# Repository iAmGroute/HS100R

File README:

# HS100R

A custom pcb for the TP-Link HS100 and HS110 smart plugs.

### Features:

  - Uses the low power nRF51 SoC (+4dBm 2.4GHz) instead of a WiFi module.
    Compatible with the popular nRF24 series modules.

  - Maintains the features of the original HS100.

  - Added sensors:

Sensor      | MPN
------------|-----
Light       | LTR-30XALS
Pressure    | DPS310
Humidity    | SI7006-A20
Temperature | SI7006-A20

  - Adds low frequency front end for mains Voltage and Current sensing, wired to the ADC of the nRF51:
    The idea is to function as a very basic oscilloscope.
    Full bandwidth: 10 KHz
      A gpio is wired to a capacitor at the input of the ADC, so that the bandwidth can be limited to around 1 KHz on demand.
    Sampling frequency: around 40 KSps (at 8 bits, around half at 10 bits)
    For the current sensing side, a current shunt resistor is required at the relay's board
    (already installed on the HS110 - 1 mOhm, will require cutting the board on the HS100 - 4 mOhm recommended)
    Two low noise PGAs (MAX9939) are added in series to give a high dynamic range.
    Max gain limitted by the front PGA's noise at around 3000x (measures a few tens of mA with 4 mOhm shunt)

  - The above can also be used to do Point-on-Wave switching:
    Turn the relay on when the instantaneous voltage is near zero
    and turn it off when the instantaneous current is near zero.
    This is done to prevend arcing on the contacts of the relay and greately improve its life span
    especially when switching heavy loads.

### Prototype pictures and screenshots:

Comming soon !

### Note about revisions:

Revisions that begin with 0 (e.g. Rev0B) are prototypes and only for reference and development.
No fully working design is available yet.

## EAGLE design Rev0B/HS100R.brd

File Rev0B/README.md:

# HS100R Rev0B  
  
Status: Unfinished  
  
TODO:  
  
  - Remove SD card slot, or reposition it.  
  
  - Fix the area of the DPS310. (maybe switch to a different IC ?)  
  
  - Reevaluate the ground layer around the DPS310.

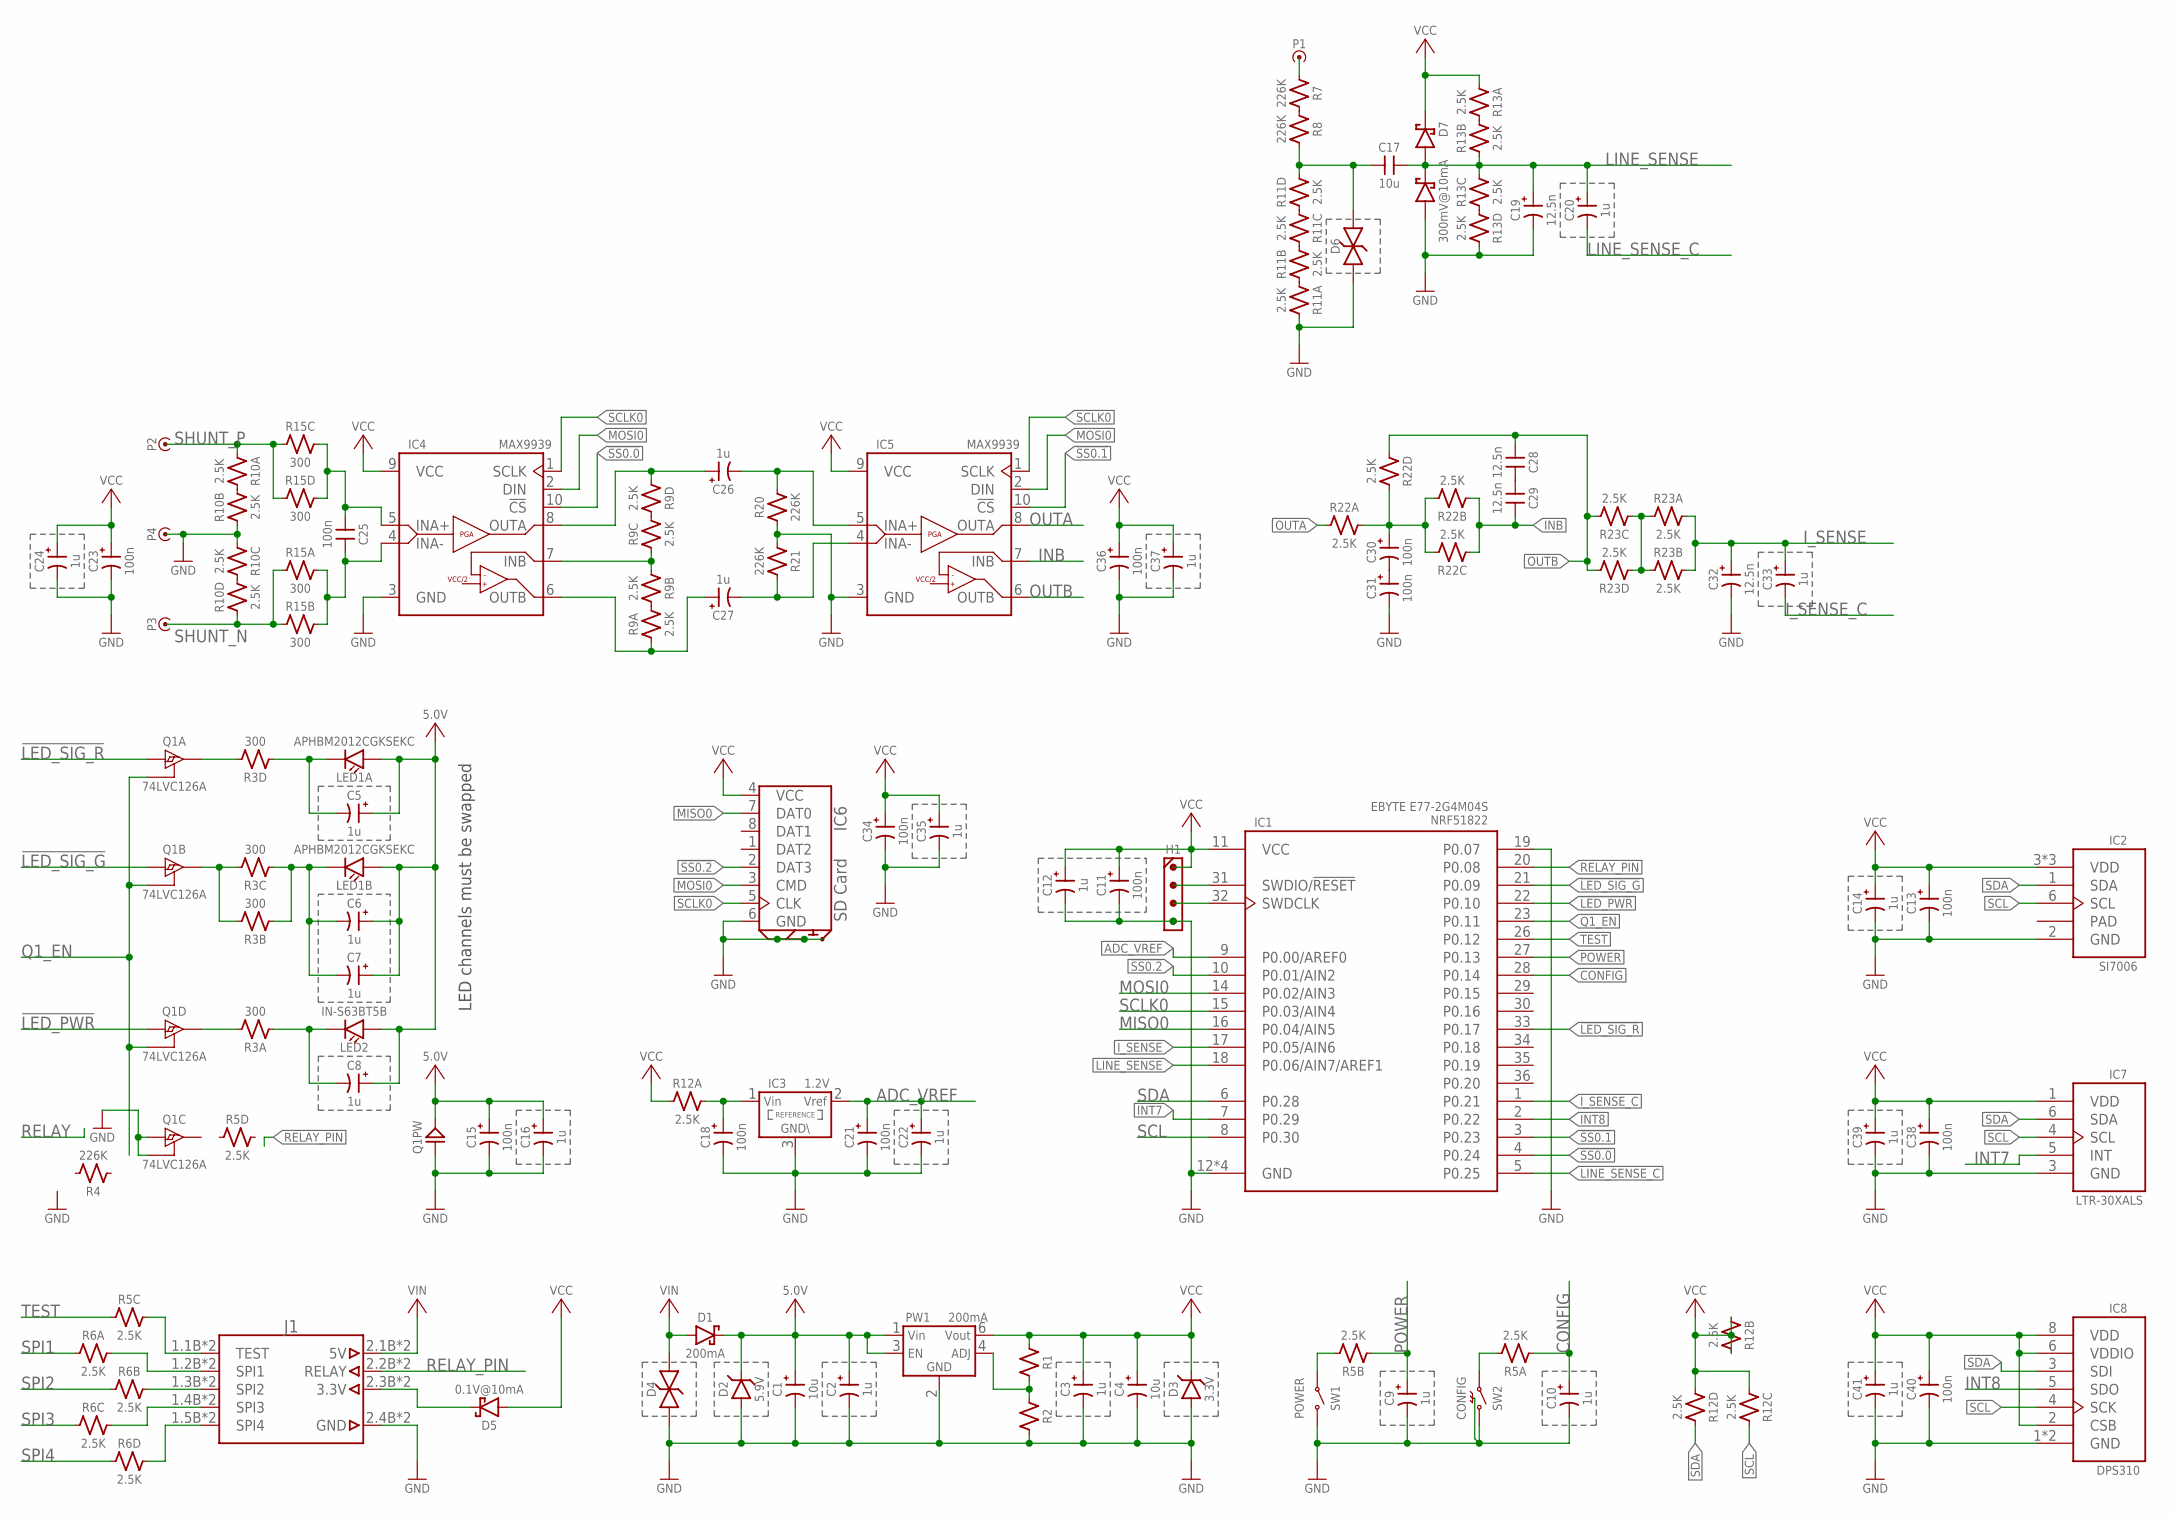
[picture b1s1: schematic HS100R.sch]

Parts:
C1, C4, C17: 10u; 1206
C2, C3, C5, C6, C7, C8, C9, C10, C12, C14, C16, C20, C22, C24, C26, C27, C33, C35, C37, C39, C41: 1u; 0805
C11, C13, C15, C18, C21, C23, C25, C30, C31, C34, C36, C38, C40: 100n; 0603
C19, C28, C29, C32: 12.5n; 0603
D1: 200mA; SOD-323F
D2: 5.9V; SOD-323F
D3: 3.3V; SOD-323F
D4, D6: DIODE_TVS_SOD-323F; SOD-323F
D5: 0.1V@10mA; SOD-323F
D7: 300mV@10mA; SOT-23
H1: HEADER_4X1-4X1; PIN_1_4X1
IC1: EBYTE_E77-2G4M04S
IC2: SI7006-A20; DFN-6_3.0_PAD
IC3: 1.2V; SOT-23
IC4, IC5: MAX9939_UMAX-10; UMAX-10
IC6: SD-CARD-MICRO-B; SD-MICRO-SPRINGED-B
IC7: LTR-30XALS
IC8: DPS310; LGA-8_2.0X2.5_0.65
J1: PCB_CONNECTOR
LED1: APHBM2012CGKSEKC; LED_DUAL-2.00X1.25
LED2: IN-S63BT5B; 0603
P1, P2, P3, P4: PIN-PIN_R_0.6; PIN_R_0.6_1X1
PW1: 200mA; SOT-23-5
Q1: 74LVC126A; SSOP-14_4.4
R1, R2: RESISTOR-0603; 0603
R3, R15: 300; 1206-QUAD
R4, R7, R8, R20, R21: 226K; 1206
R5, R6, R9, R10, R11, R12, R13, R22, R23: 2.5K; 1206-QUAD
SW1: POWER; GULLWING-4_4.2X3.2
SW2: CONFIG; SWITCH-RA_4.5X4.5

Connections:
5.0V: C1.C, C2.C, C5.C, C6.C, C7.C, C8.C, C15.C, C16.C, D1.C, D2.C, LED1.A1 (ANODE), LED1.A2 (ANODE), LED2.A (ANODE), PW1.1 (VIN), PW1.3 (EN), Q1.14 (VCC)
!LED_PWR: IC1.22 (P0.10), Q1.12 (IN)
!LED_SIG_G: IC1.21 (P0.09), Q1.5 (IN)
!LED_SIG_R: IC1.33 (P0.17), Q1.2 (IN)
!SS0.0: IC1.4 (P0.24), IC4.10 (!CS)
!SS0.1: IC1.3 (P0.23), IC5.10 (!CS)
!SS0.2: IC1.10 (P0.01/AIN2), IC6.2 (DAT3)
ADC_VREF: C21.C, C22.C, IC1.9 (P0.00/AREF0), IC3.2 (VOUT)
CONFIG: C10.C, IC1.28 (P0.14), R5.1
GND: C1.A (N), C2.A (N), C3.A (N), C4.A (N), C9.A (N), C10.A (N), C11.A (N), C12.A (N), C13.A (N), C14.A (N), C15.A (N), C16.A (N), C18.A (N), C19.A (N), C21.A (N), C22.A (N), C23.A (N), C24.A (N), C31.A (N), C32.A (N), C34.A (N), C35.A (N), C36.A (N), C37.A (N), C38.A (N), C39.A (N), C40.A (N), C41.A (N), D2.A, D3.A, D4.A (1), D6.A (1), D7.1 (A), H1.1.4, IC1.12 (GND), IC1.13 (GND), IC1.19 (P0.07), IC1.24 (GND), IC1.25 (GND), IC2.2 (GND), IC3.3 (GND), IC4.3 (GND), IC5.3 (GND), IC6.6 (GND), IC6.DETECT (DETECT1), IC6.SHIELD1 (SHIELD), IC6.SHIELD2 (SHIELD), IC6.SHIELD3 (SHIELD), IC6.SHIELD4 (DETECT2), IC7.3 (GND), IC8.1 (GND), IC8.7 (GND), J1.2.4B (GND), J1.2.4T (GND), P4.1.1, PW1.2 (GND), Q1.7 (GND), Q1.9 (IN), Q1.10 (OE), R2.C (2), R10.2 (1), R10.3 (1), R11.8 (2), R13.5 (2), R20.A (1), R21.A (1), SW1.3 (2), SW1.4 (2), SW2.2, SW2.SHIELD
INB: C29.C (2), IC5.7 (INB), R22.2 (1), R22.3 (1)
INT7: IC1.7 (P0.29), IC7.5 (INT)
INT8: IC1.2 (P0.22), IC8.5 (SDO)
I_SENSE: C32.C, C33.C, IC1.17 (P0.05/AIN6), R23.7 (2), R23.8 (2)
I_SENSE_C: C33.A (N), IC1.1 (P0.21)
LINE_SENSE: C17.C (2), C19.C, C20.C, D7.3 (COMMON), IC1.18 (P0.06/AIN7/AREF1), R13.2 (1), R13.6 (2)
LINE_SENSE_C: C20.A (N), IC1.5 (P0.25)
MISO0: IC1.16 (P0.04/AIN5), IC6.7 (DAT0)
MOSI0: IC1.14 (P0.02/AIN3), IC4.2 (DIN), IC5.2 (DIN), IC6.3 (CMD)
unnamed: D5.C, J1.2.3B (3.3V), J1.2.3T (3.3V)
unnamed: Q1.3 (OUT), R3.5 (2)
unnamed: PW1.4 (ADJ), R1.C (2), R2.A (1)
unnamed: C5.A (N), LED1.K1 (CATHODE), R3.4 (1)
unnamed: Q1.11 (OUT), R3.8 (2)
unnamed: Q1.6 (OUT), R3.6 (2), R3.7 (2)
unnamed: C8.A (N), LED2.C (CATHODE), R3.1
unnamed: J1.1.2B (SPI1), J1.1.2T (SPI1), R6.8 (2)
unnamed: C6.A (N), C7.A (N), LED1.K2 (CATHODE), R3.2 (1), R3.3 (1)
unnamed: R5.7 (2), SW1.1, SW1.2 (1)
unnamed: R11.3 (1), R11.4 (1)
unnamed: R5.8 (2), SW2.1
unnamed: J1.1.1B (TEST), J1.1.1T (TEST), R5.6 (2)
unnamed: J1.1.3B (SPI2), J1.1.3T (SPI2), R6.7 (2)
unnamed: J1.1.4B (SPI3), J1.1.4T (SPI3), R6.6 (2)
unnamed: J1.1.5B (SPI4), J1.1.5T (SPI4), R6.5 (2)
unnamed: P1.1.1, R7.A (1)
unnamed: R7.C (2), R8.A (1)
unnamed: H1.1.3, IC1.32 (SWDCLK)
unnamed: H1.1.2, IC1.31 (SWDIO/!RESET)
unnamed: C17.A (1), D6.C (2), R8.C (2), R11.5 (2)
unnamed: C18.C, IC3.1 (VIN), R12.8 (2)
unnamed: R13.7 (2), R13.8 (2)
unnamed: R13.3 (1), R13.4 (1)
unnamed: C25.A (1), IC4.5 (INA+), R15.5 (2), R15.6 (2)
unnamed: C25.C (2), IC4.4 (INA-), R15.7 (2), R15.8 (2)
unnamed: IC4.7 (INB), R9.2 (1), R9.3 (1)
unnamed: C28.C (2), C29.A (1)
unnamed: R11.6 (2), R11.7 (2)
unnamed: C30.C, R22.5 (2), R22.6 (2), R22.7 (2), R22.8 (2)
unnamed: C26.A (N), IC5.5 (INA+), R20.C (2)
unnamed: R23.1, R23.2 (1), R23.3 (1), R23.4 (1)
unnamed: C27.A (N), IC5.4 (INA-), R21.C (2)
unnamed: C26.C, IC4.8 (OUTA), R9.4 (1)
unnamed: R9.5 (2), R9.6 (2)
unnamed: C30.A (N), C31.C
unnamed: R9.7 (2), R9.8 (2)
unnamed: C27.C, IC4.6 (OUTB), R9.1
unnamed: R10.5 (2), R10.6 (2)
unnamed: R10.7 (2), R10.8 (2)
unnamed: R11.1, R11.2 (1)
OUTA: IC5.8 (OUTA), R22.1
OUTB: C28.A (1), IC5.6 (OUTB), R22.4 (1), R23.5 (2), R23.6 (2)
POWER: C9.C, IC1.27 (P0.13), R5.2 (1)
Q1_EN: IC1.23 (P0.11), Q1.1 (OE), Q1.4 (OE), Q1.13 (OE)
RELAY_PIN: IC1.20 (P0.08), J1.2.2B (RELAY), J1.2.2T (RELAY)
SCL: IC1.8 (P0.30), IC2.6 (SCL), IC7.4 (SCL), IC8.4 (SCK), R12.6 (2)
SCLK0: IC1.15 (P0.03/AIN4), IC4.1 (SCLK), IC5.1 (SCLK), IC6.5 (CLK)
SDA: IC1.6 (P0.28), IC2.1 (SDA), IC7.6 (SDA), IC8.3 (SDI), R12.5 (2)
SHUNT_N: P3.1.1, R10.4 (1), R15.1, R15.2 (1)
SHUNT_P: P2.1.1, R10.1, R15.3 (1), R15.4 (1)
SPI1: R6.1
SPI2: R6.2 (1)
SPI3: R6.3 (1)
SPI4: R6.4 (1)
TEST: IC1.26 (P0.12), R5.3 (1)
VCC: C3.C, C4.C, C11.C, C12.C, C13.C, C14.C, C23.C, C24.C, C34.C, C35.C, C36.C, C37.C, C38.C, C39.C, C40.C, C41.C, D3.C, D5.A, D7.2 (C), H1.1.1, IC1.11 (VCC), IC2.3 (VDD), IC2.4 (VDD), IC2.5 (VDD), IC4.9 (VCC), IC5.9 (VCC), IC6.4 (VCC), IC7.1 (VDD), IC8.2 (CSB), IC8.6 (VDDIO), IC8.8 (VDD), PW1.6 (VOUT), R1.A (1), R12.1, R12.2 (1), R12.3 (1), R12.4 (1), R12.7 (2), R13.1
VIN: D1.A, D4.C (2), J1.2.1B (5V), J1.2.1T (5V)

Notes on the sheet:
LED channels must be swapped

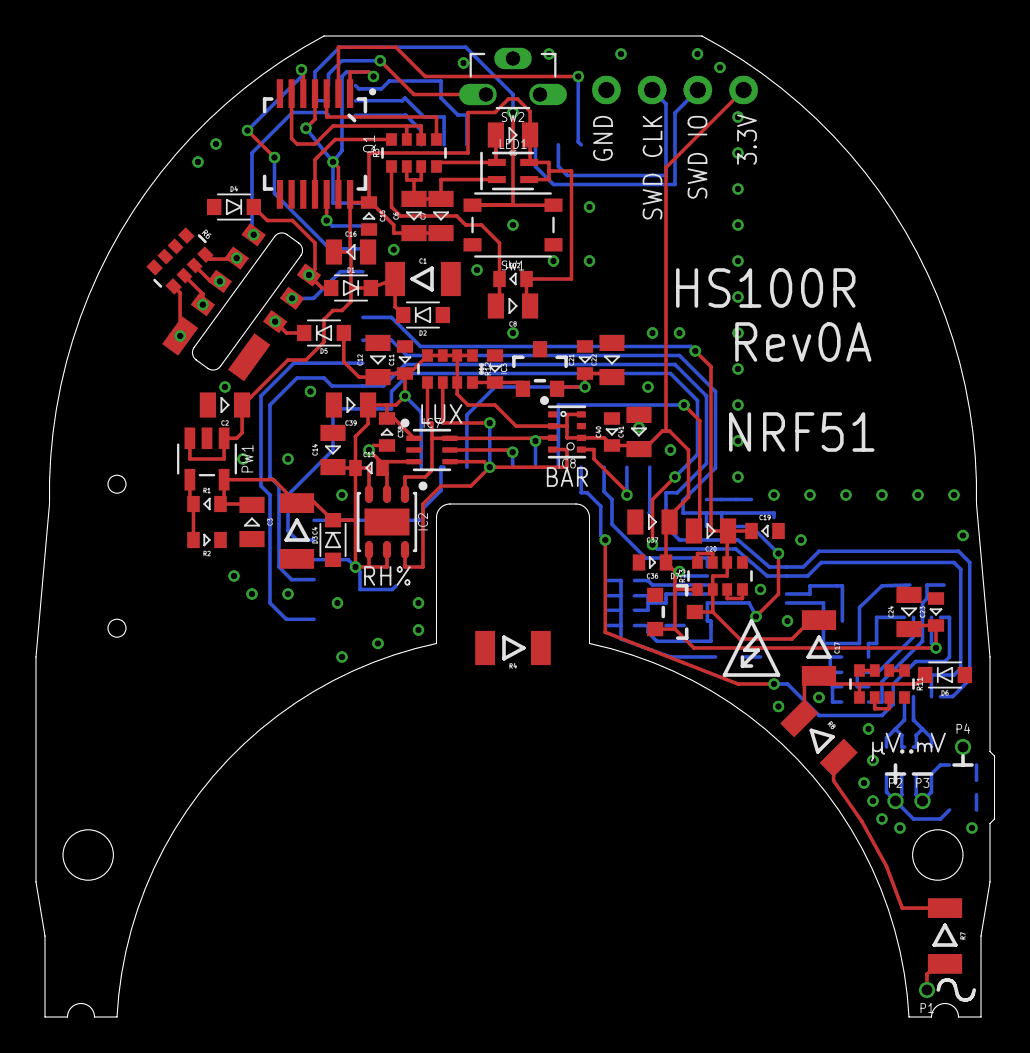
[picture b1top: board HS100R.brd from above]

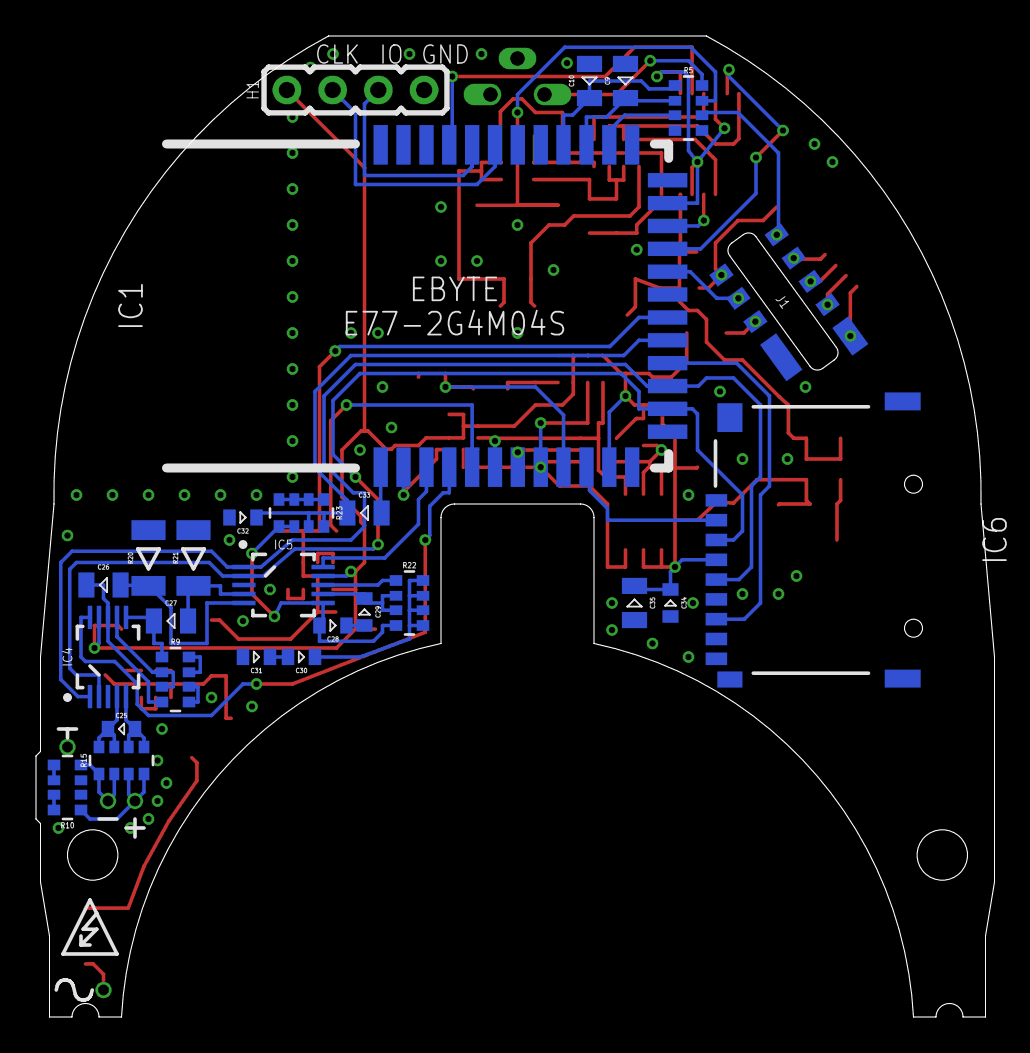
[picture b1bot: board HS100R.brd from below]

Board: 2 copper layers, 53.2 x 54.5 mm, 86 parts (27 on the bottom side), 73 nets.

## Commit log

2019-05-14 Init
2022-04-30 Upload images
